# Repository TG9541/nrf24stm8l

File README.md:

# nrf24stm8l

STM8L051F3P6 board with an nRF24L01+ module, a 32.768KHz crystal, and a CR2032 battery holder for prototyping wireless sensors. [STM8 eForth](https://github.com/TG9541/stm8ef/) support for nRF24L01+ (or SI24R1) is [work in progress](https://github.com/VK6TT/stm8ef-nRF24L01-).

The HackaDay project [STM8 eForth Wireless Sensor][HAD1] explores using this PCB.

[HAD1]: https://hackaday.io/project/158459-stm8-eforth-wireless-sensor

[][HAD1]

PCB can be ordered from OSHPark (3pcs for about $4):

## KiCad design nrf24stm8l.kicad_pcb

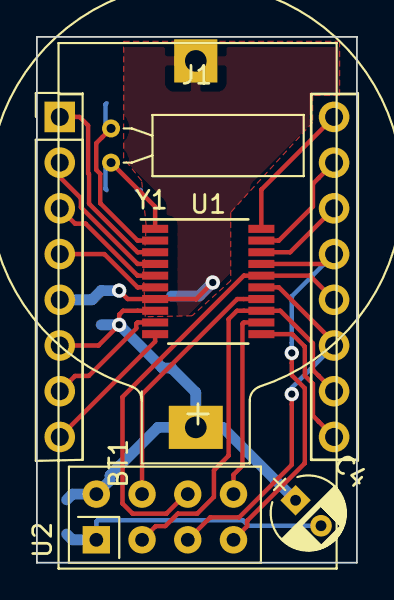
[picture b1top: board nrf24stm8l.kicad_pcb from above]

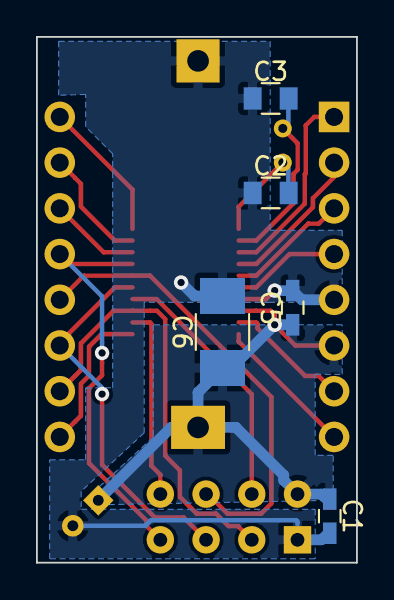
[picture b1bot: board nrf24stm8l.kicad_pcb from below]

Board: 2 copper layers, 17.8 x 29.2 mm, 11 parts (5 on the bottom side), 20 nets.

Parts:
BT1: CR2032; AliExpress_CR2032
C1, C5: 100nF; C_0603_HandSoldering
C2, C3: 8pF; C_0805
C4: 33uF; CP_Radial_D4.0mm_P2.00mm
C6: 33uF; C_1210_HandSoldering
J1: Conn_02x08_Counter_Clockwise; Pin_Header_Straight_2x08_6wide_Pitch2.54mm
U1: STM8L051F3P; TSSOP-20_4.4x6.5mm_Pitch0.65mm
U2: NRF24L01_Breakout; nRF24L01_Breakout
Y1: Q32KHz; Crystal_C38-LF_d3.0mm_l8.0mm_Horizontal

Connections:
/A0: J1.1, U1.3
/A1: J1.2, U1.4
/A2: J1.3, U1.5
/A3: J1.4, U1.6
/B0: J1.8, U1.10
/B1: J1.9, U1.11
/B2: U1.12, U2.8
/B3: J1.10, U1.13, U2.3
/B4: U1.14, U2.4
/B5: J1.11, U1.15, U2.5
/B6: J1.12, U1.16, U2.6
/B7: J1.13, U1.17, U2.7
/C0: J1.14, U1.18
/C1: J1.15, U1.19
/C4: J1.16, U1.20
/D0: J1.7, U1.9
GND: BT1.2, C1.2, C2.1, C3.1, C4.2, C5.2, C6.2, J1.5, U1.7, U2.1
unnamed: C2.2, U1.1, Y1.1
unnamed: C3.2, U1.2, Y1.2
VDD: BT1.1, C1.1, C4.1, C5.1, C6.1, J1.6, U1.8, U2.2

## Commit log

2018-05-13 OSHPark link added
2018-05-20 Update README.md
    Add links.
2020-06-19 KiCad files added
